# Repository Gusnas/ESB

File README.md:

# SB-20

Arduino and node-red tests for ESB

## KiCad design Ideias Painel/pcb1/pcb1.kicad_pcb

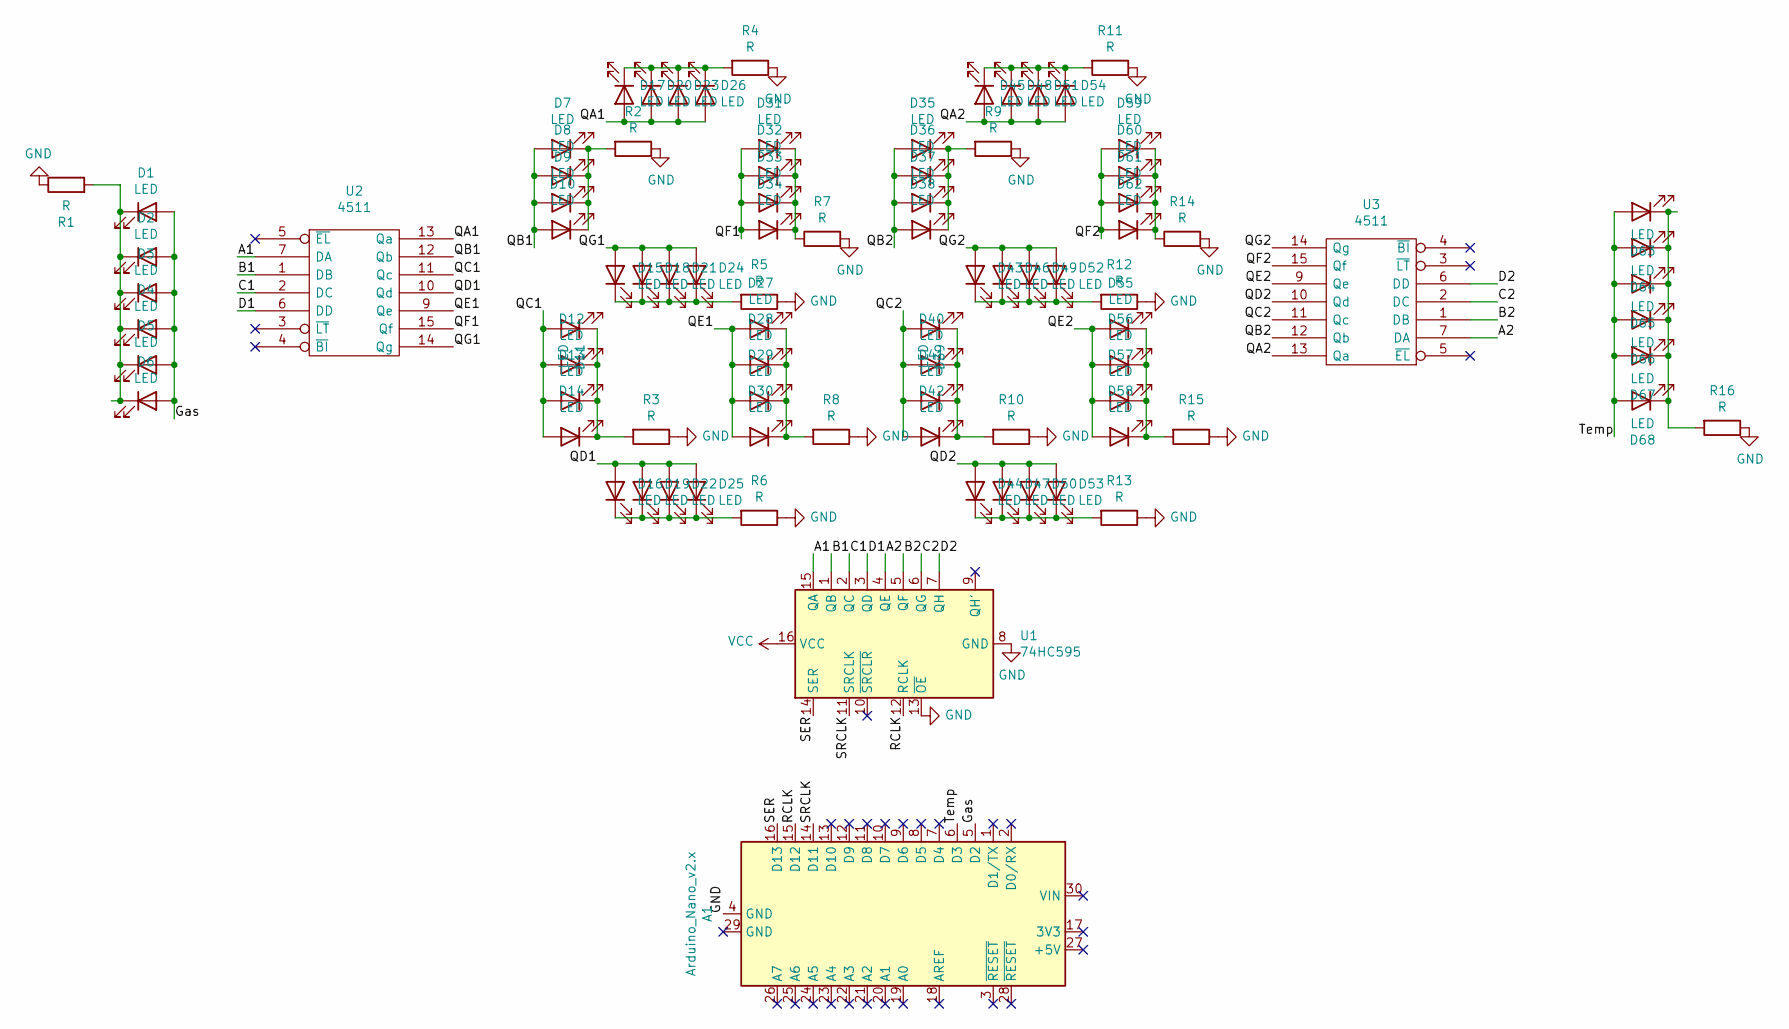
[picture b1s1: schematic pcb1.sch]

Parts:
A1: Arduino_Nano_v2.x; Arduino_Nano
D1, D2, D3, D4, D5, D6, D7, D8, D9, D10, D11, D12, D13, D14, D15, D16, D17, D18, D19, D20, D21, D22, D23, D24, D25, D26, D27, D28, D29, D30, D31, D32, D33, D34, D35, D36, D37, D38, D39, D40, D41, D42, D43, D44, D45, D46, D47, D48, D49, D50, D51, D52, D53, D54, D55, D56, D57, D58, D59, D60, D61, D62, D63, D64, D65, D66, D67, D68: LED; LED_D3.0mm
R1, R2, R3, R4, R5, R6, R7, R8, R9, R10, R11, R12, R13, R14, R15, R16: R; R_Axial_DIN0204_L3.6mm_D1.6mm_P5.08mm_Horizontal
U1: 74HC595; DIP-16_W7.62mm
U2, U3: 4511; DIP-16_W7.62mm

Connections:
/A1: U1.15 (QA), U2.7 (DA)
/A2: U1.4 (QE), U3.7 (DA)
/B1: U1.1 (QB), U2.1 (DB)
/B2: U1.5 (QF), U3.1 (DB)
/C1: U1.2 (QC), U2.2 (DC)
/C2: U1.6 (QG), U3.2 (DC)
/D1: U1.3 (QD), U2.6 (DD)
/D2: U1.7 (QH), U3.6 (DD)
/Gas: A1.5 (D2), D1.2 (A), D2.2 (A), D3.2 (A), D4.2 (A), D5.2 (A), D6.2 (A)
/QA1: D17.2 (A), D20.2 (A), D23.2 (A), D26.2 (A), U2.13 (Qa)
/QA2: D45.2 (A), D48.2 (A), D51.2 (A), D54.2 (A), U3.13 (Qa)
/QB1: D7.2 (A), D8.2 (A), D9.2 (A), D10.2 (A), U2.12 (Qb)
/QB2: D35.2 (A), D36.2 (A), D37.2 (A), D38.2 (A), U3.12 (Qb)
/QC1: D11.2 (A), D12.2 (A), D13.2 (A), D14.2 (A), U2.11 (Qc)
/QC2: D39.2 (A), D40.2 (A), D41.2 (A), D42.2 (A), U3.11 (Qc)
/QD1: D16.2 (A), D19.2 (A), D22.2 (A), D25.2 (A), U2.10 (Qd)
/QD2: D44.2 (A), D47.2 (A), D50.2 (A), D53.2 (A), U3.10 (Qd)
/QE1: D27.2 (A), D28.2 (A), D29.2 (A), D30.2 (A), U2.9 (Qe)
/QE2: D55.2 (A), D56.2 (A), D57.2 (A), D58.2 (A), U3.9 (Qe)
/QF1: D31.2 (A), D32.2 (A), D33.2 (A), D34.2 (A), U2.15 (Qf)
/QF2: D59.2 (A), D60.2 (A), D61.2 (A), D62.2 (A), U3.15 (Qf)
/QG1: D15.2 (A), D18.2 (A), D21.2 (A), D24.2 (A), U2.14 (Qg)
/QG2: D43.2 (A), D46.2 (A), D49.2 (A), D52.2 (A), U3.14 (Qg)
/RCLK: A1.15 (D12), U1.12 (RCLK)
/SER: A1.16 (D13), U1.14 (SER)
/SRCLK: A1.14 (D11), U1.11 (SRCLK)
/Temp: A1.6 (D3), D63.2 (A), D64.2 (A), D65.2 (A), D66.2 (A), D67.2 (A), D68.2 (A)
GND: R1.1, R2.1, R3.1, R4.1, R5.1, R6.1, R7.2, R8.1, R9.1, R10.1, R11.1, R12.1, R13.1, R14.2, R15.1, R16.1, U1.8 (GND), U1.13 (~OE)
unnamed: D1.1 (K), D2.1 (K), D3.1 (K), D4.1 (K), D5.1 (K), D6.1 (K), R1.2
unnamed: D7.1 (K), D8.1 (K), D9.1 (K), D10.1 (K), R2.2
unnamed: D11.1 (K), D12.1 (K), D13.1 (K), D14.1 (K), R3.2
unnamed: D15.1 (K), D18.1 (K), D21.1 (K), D24.1 (K), R5.2
unnamed: D16.1 (K), D19.1 (K), D22.1 (K), D25.1 (K), R6.2
unnamed: D17.1 (K), D20.1 (K), D23.1 (K), D26.1 (K), R4.2
unnamed: D27.1 (K), D28.1 (K), D29.1 (K), D30.1 (K), R8.2
unnamed: D31.1 (K), D32.1 (K), D33.1 (K), D34.1 (K), R7.1
unnamed: D35.1 (K), D36.1 (K), D37.1 (K), D38.1 (K), R9.2
unnamed: D39.1 (K), D40.1 (K), D41.1 (K), D42.1 (K), R10.2
unnamed: D43.1 (K), D46.1 (K), D49.1 (K), D52.1 (K), R12.2
unnamed: D44.1 (K), D47.1 (K), D50.1 (K), D53.1 (K), R13.2
unnamed: D45.1 (K), D48.1 (K), D51.1 (K), D54.1 (K), R11.2
unnamed: D55.1 (K), D56.1 (K), D57.1 (K), D58.1 (K), R15.2
unnamed: D59.1 (K), D60.1 (K), D61.1 (K), D62.1 (K), R14.1
unnamed: D63.1 (K), D64.1 (K), D65.1 (K), D66.1 (K), D67.1 (K), D68.1 (K), R16.2
VCC: U1.16 (VCC)
Vdd: U2.16 (Vdd), U3.16 (Vdd)
Vss: U2.8 (Vss), U3.8 (Vss)

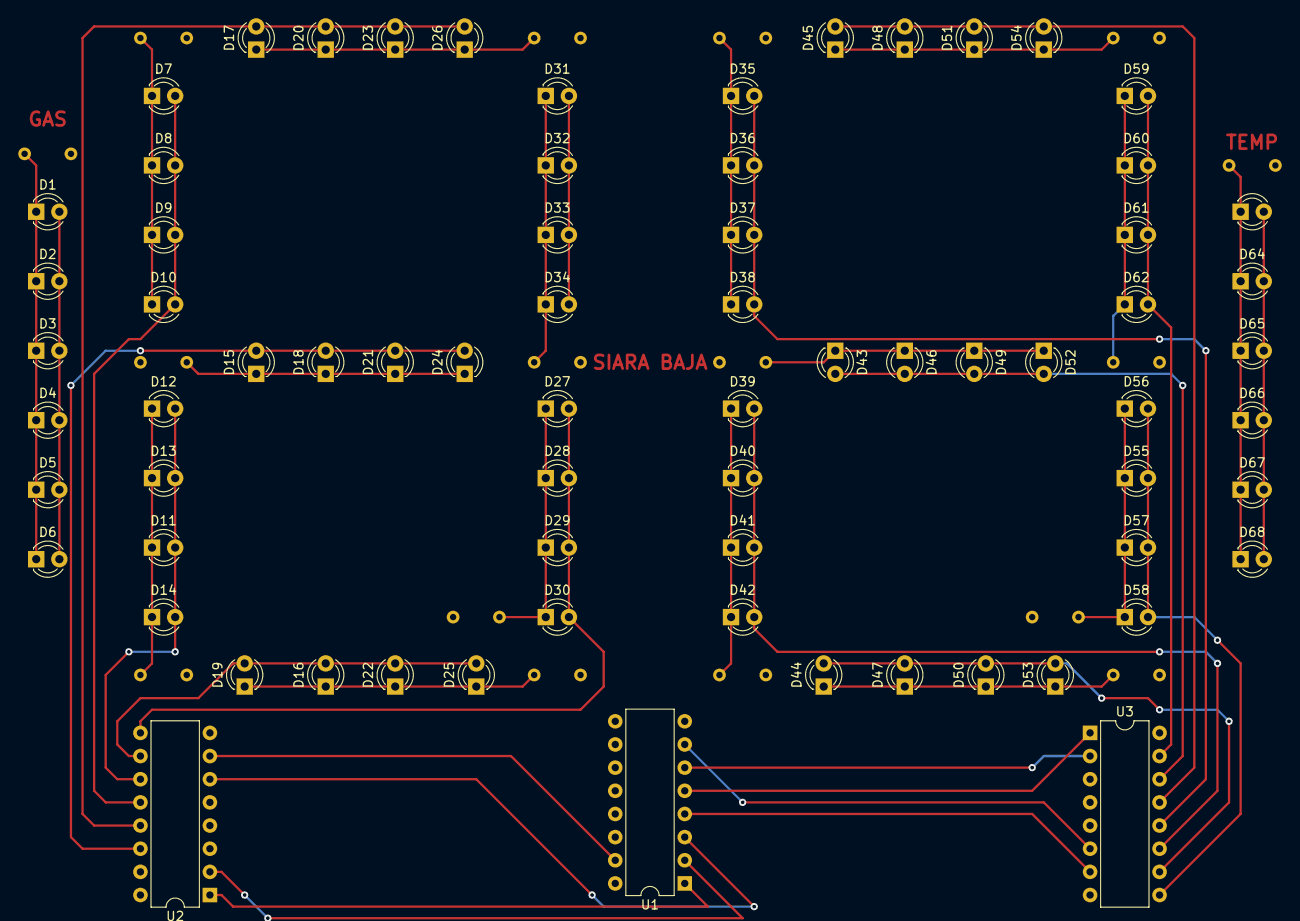
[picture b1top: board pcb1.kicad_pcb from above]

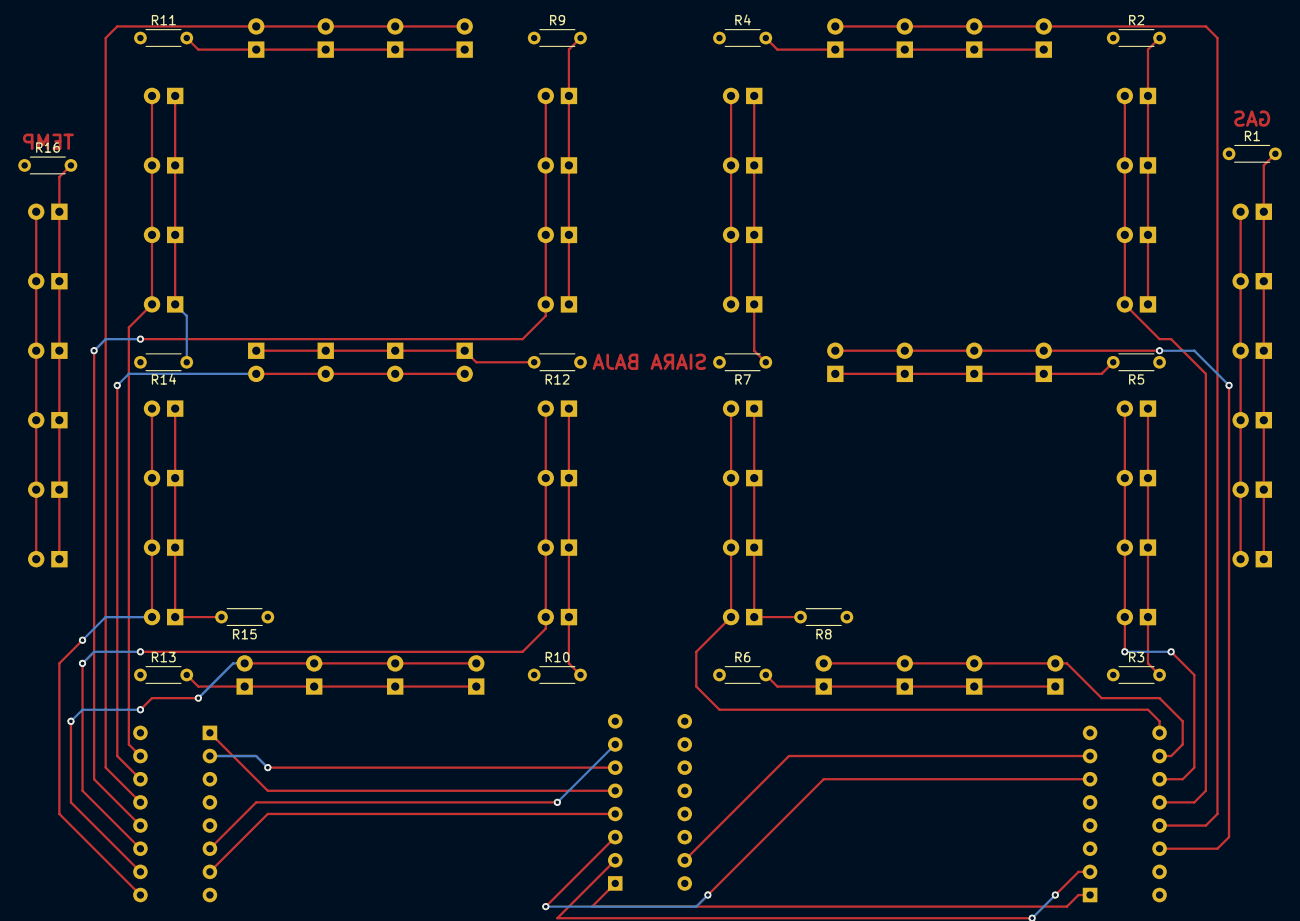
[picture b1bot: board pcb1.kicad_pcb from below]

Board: 2 copper layers, 87 parts (16 on the bottom side), 43 nets.

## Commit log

2020-06-10 Potentiometer
    Arduino and node-red codes
2021-05-06 Rename flows.json to SB20-Dashboard.json
